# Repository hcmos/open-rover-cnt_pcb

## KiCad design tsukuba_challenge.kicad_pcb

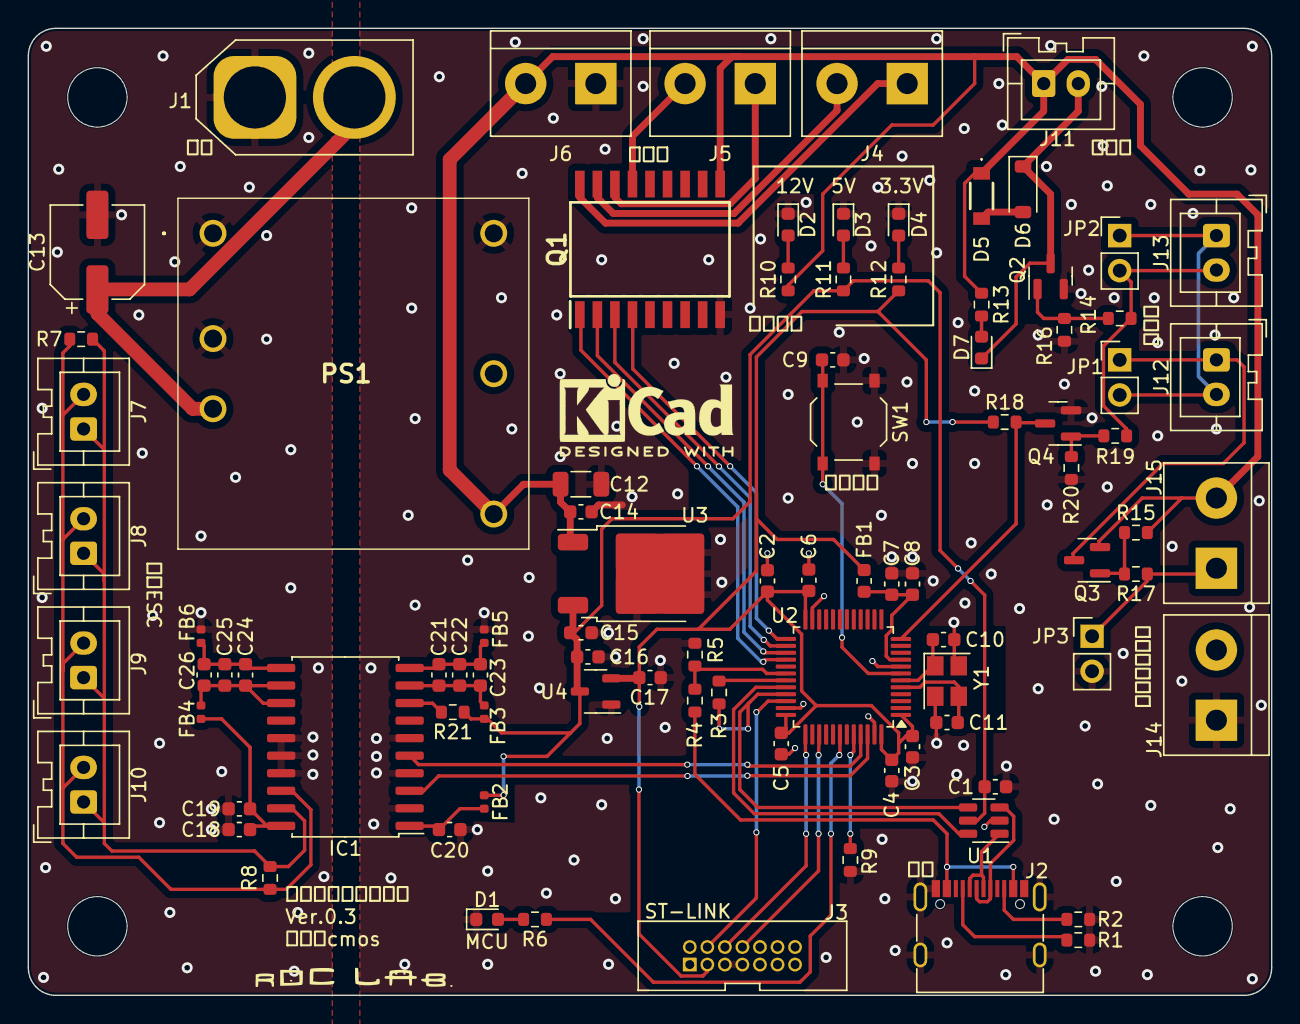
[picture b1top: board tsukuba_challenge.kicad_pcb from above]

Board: 2 copper layers, 90.0 x 70.0 mm, 94 parts (0 on the bottom side), 58 nets.

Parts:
C1, C3, C4, C5, C6, C8, C9, C15, C18, C20: 0.1u; C_0603_1608Metric
C2, C19, C21, C26: 10u; C_0603_1608Metric
C7, C16, C17, C22, C25: 1u; C_0603_1608Metric
C10, C11: 10p; C_0603_1608Metric
C12: 22u; C_1206_3216Metric
C13: 100u; CP_Elec_6.3x7.7
C14: 0.47u; C_0603_1608Metric
C23, C24: 10n; C_0603_1608Metric
D1: LED_MCU; LED_0603_1608Metric
D2, D3, D4, D7: LED; LED_0603_1608Metric
D5: D; SOD-123FL
D6: D_Zener; D_SOD-123
FB1: FerriteBead; L_0603_1608Metric
FB2, FB3, FB4, FB5, FB6: FerriteBead; L_0402_1005Metric
H1, H2, H3, H4: MountingHole; MountingHole_4.3mm_M4
IC1: ISOW1044BDFMR; SOIC-20W_7.5x12.8mm_P1.27mm
J1: PWR_BATT; AMASS_XT60-M_1x02_P7.20mm_Vertical
J2: USB_C_Receptacle_USB2.0; USB_C_Receptacle_G-Switch_GT-USB-7010ASV
J3: ST-LINK; JTAG_BOX_CONN
J4, J5, J6: INDICATOR; TerminalBlock_bornier-2_P5.08mm
J7, J8, J9, J10: CAN; JST_XA_B02B-XASK-1_1x02_P2.50mm_Vertical
J11: Relay; JST_XA_B02B-XASK-1_1x02_P2.50mm_Vertical
J12, J13: EMS_SW; JST_XA_B02B-XASK-1_1x02_P2.50mm_Vertical
J14, J15: Remote_SW; TerminalBlock_bornier-2_P5.08mm
JP1, JP2, JP3: EMS_Jumper; PinHeader_1x02_P2.54mm_Vertical
PS1: CCG30-24-12S; CCG304815S
Q1: TBD62083AFWG_Z,EHZ; SOIC127P1032X285-18N
Q2, Q4: Q_NMOS_GSD; SOT-23
Q3: Q_PMOS_GSD; SOT-23
R1, R2: 5.1k; R_0603_1608Metric
R3: 1.5k; R_0603_1608Metric
R4: 33k; R_0603_1608Metric
R5: 82k; R_0603_1608Metric
R6, R12: 1.2k; R_0603_1608Metric
R7, R8: 120; R_0603_1608Metric
R9, R10, R13, R15, R16, R18, R20: 10k; R_0603_1608Metric
R11: 3.3k; R_0603_1608Metric
R14, R19: 100; R_0603_1608Metric
R17: 2k; R_0603_1608Metric
R21: 4.7k; R_0603_1608Metric
SW1: SPST_SW; SW_Push_1P1T_XKB_TS-1187A
U1: USBLC6-2SC6; SOT-23-6
U2: STM32F302CBTx; LQFP-48_7x7mm_P0.5mm
U3: L7805; TO-252-2
U4: XC6206P332MR; SOT-23-3
Y1: 12MHz; Crystal_SMD_3225-4Pin_3.2x2.5mm

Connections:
+3.3V: C2.1, C3.1, C4.1, C5.1, C6.1, C17.1, FB1.1, J3.3, R12.1, R18.1, U2.1 (VBAT), U2.24 (VDD), U2.36 (VDD), U2.48 (VDD), U4.2 (VO)
+5V: C1.2, C15.1, C16.1, FB2.1, FB3.1, R11.1, R21.1, U1.5 (VBUS), U3.3 (OUT), U4.3 (VI)
+12V: C12.1, C14.1, D5.1 (K), J6.2, J11.1, J15.2, PS1.4 (+VOUT), Q1.10 (COMMON), Q3.2 (S), R10.1, R13.1, R15.2, U3.1 (IN)
+BATT: C13.1, J1.2, PS1.3 (+VIN)
/CAN_Transceiver/CAN_H: IC1.19 (CANH), J7.1, J8.1, J9.1, J10.1, R7.1, R8.1
/CAN_Transceiver/CAN_L: IC1.18 (CANL), J7.2, J8.2, J9.2, J10.2, R7.2, R8.2
/CAN_Transceiver/CAN_RX: IC1.5 (RXD), U2.45 (PB8)
/CAN_Transceiver/CAN_TX: IC1.3 (TXD), U2.46 (PB9)
/D+_IN: J2.A6 (D+), J2.B6 (D+), U1.3 (I/O2)
/D+_OUT: R3.1, U1.4 (I/O2), U2.33 (PA12)
/D-_IN: J2.A7 (D-), J2.B7 (D-), U1.1 (I/O1)
/D-_OUT: U1.6 (I/O1), U2.32 (PA11)
/EMS/MCU_EMS_OBSERVE: Q4.3 (D), R18.2, U2.12 (PA2)
/MCU_CYCLE_LED: R6.1, U2.42 (PB6)
/STM32F302/INDICATOR_BUZZER: Q1.4 (I4), U2.25 (PB12)
/STM32F302/INDICATOR_GREEN: Q1.3 (I3), U2.26 (PB13)
/STM32F302/INDICATOR_RED: Q1.1 (I1), U2.28 (PB15)
/STM32F302/INDICATOR_YELLOW: Q1.2 (I2), U2.27 (PB14)
/STM32F302/SWCLK: J3.6, U2.37 (PA14)
/STM32F302/SWDIO: J3.4, U2.34 (PA13)
/STM32F302/SWO: J3.8, U2.39 (PB3)
/STM32F302/USB_PULLUP: R3.2, U2.31 (PA10)
/STM32F302/USB_VBUS: R4.2, R5.2, U2.30 (PA9)
/USB_VBUS: J2.A4 (VBUS), J2.A9 (VBUS), J2.B4 (VBUS), J2.B9 (VBUS), R4.1
GND: C1.1, C2.2, C3.2, C4.2, C5.2, C6.2, C7.1, C8.1, C9.2, C10.2, C11.2, C12.2, C14.2, C15.2, C16.2, C17.2, C20.2, D1.1 (K), D2.1 (K), D3.1 (K), D4.1 (K), FB5.1, IC1.2 (IN), IC1.4 (STB), IC1.6 (GNDIO), J2.A1 (GND), J2.A12 (GND), J2.B1 (GND), J2.B12 (GND), J2.S1 (SHIELD), J3.5, J3.7, J6.1, J14.1, JP3.2 (B), PS1.6 (-VOUT), Q1.9 (GND), Q2.2 (S), Q4.2 (S), R1.2, R2.2, R5.1, R9.2, R16.1, R20.2, SW1.1 (A), U1.2 (GND), U2.8 (VSSA), U2.23 (VSS), U2.35 (VSS), U2.47 (VSS), U3.2 (GND), U4.1 (GND), Y1.2, Y1.4
GNDPWR: C13.2, C18.2, C19.2, FB6.2, IC1.15 (GISOIN_1), IC1.16 (GISOIN_2), IC1.17 (GISOIN_3), J1.1, PS1.1 (RC), PS1.2 (-VIN)
unnamed: D1.2 (A), R6.2
unnamed: D2.2 (A), R10.2
unnamed: D3.2 (A), R11.2
unnamed: D4.2 (A), R12.2
unnamed: D5.2 (A), D6.2 (A)
unnamed: D6.1 (K), D7.1 (K), J11.2, Q2.3 (D)
unnamed: D7.2 (A), R13.2
unnamed: IC1.8 (EN/FLT), R21.2
unnamed: C21.2, C22.2, C23.2, FB5.2, IC1.10 (GND1)
unnamed: C24.2, C25.2, C26.2, FB6.1, IC1.11 (GND2)
unnamed: C21.1, C22.1, C23.1, FB3.2, IC1.9 (VDD)
unnamed: C20.1, FB2.2, IC1.1 (VIO)
unnamed: C18.1, C19.1, FB4.2, IC1.20 (VISOIN)
unnamed: C24.1, C25.1, C26.1, FB4.1, IC1.12 (VISOOUT), IC1.13 (VSIN)
unnamed: J2.A5 (CC1), R1.1
unnamed: J2.B5 (CC2), R2.1
unnamed: J4.1, Q1.18 (O1)
unnamed: J4.2, Q1.17 (O2)
unnamed: J5.1, Q1.16 (O3)
unnamed: J5.2, Q1.15 (O4)
unnamed: J12.1, JP1.1 (A), Q3.3 (D)
unnamed: J12.2, J13.1, JP1.2 (B), JP2.1 (A)
unnamed: J13.2, JP2.2 (B), R14.1, R19.2
unnamed: J15.1, JP3.1 (A), R17.1
unnamed: Q2.1 (G), R14.2, R16.2
unnamed: Q3.1 (G), R15.1, R17.2
unnamed: Q4.1 (G), R19.1, R20.1
unnamed: C9.1, SW1.2 (B), U2.7 (NRST)
unnamed: R9.1, U2.44 (BOOT0)
unnamed: C11.1, U2.5 (PF0), Y1.3
unnamed: C10.1, U2.6 (PF1), Y1.1
VDDA: C7.2, C8.2, FB1.2, U2.9 (VDDA)

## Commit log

2025-03-30 ✨feat:first ci
2025-03-30 3/30
2025-04-02 4/2(1)
2025-04-02 4/2(2)
2025-04-04 🐛fix:
2025-04-12 4/12
2025-04-12 4/13 product update
2025-04-15 product data
2025-04-27 ✨feat:f302
2025-07-19 6/29
2025-07-19 7/19
